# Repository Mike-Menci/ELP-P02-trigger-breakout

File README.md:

To trigger the camera as the nozzle passes over the vision area, your motion controller (e.g., Duet, Smoothieboard, or custom firmware) must:
Know the exact position of the nozzle.
Send a trigger pulse when the nozzle is centered over the camera FOV.
Optionally, queue the trigger slightly ahead to compensate for latency.
Example (pseudo-code):
if (motor->within_trigger_area()) {
    if (!trig_condition) {
        pull_camera_trig(); // Send 1.8V pulse
        trig_condition = true;
    }
}

This logic can be added to the stepper interrupt loop or motion planner in your firmware.

**** OpenPnP Software Integration
OpenPnP does not yet natively support on-the-fly vision, but you can prototype it with the following steps:
** Step-by-Step Integration Plan:
Disable Bottom Vision Settling
In OpenPnP, disable the default bottom vision settling behavior to allow motion to continue.
Use External Trigger Mode
Configure the camera to only capture when triggered (via hardware trigger), not on a free-running stream.
Capture Image Asynchronously
After triggering, store the image in a buffer (possibly on a companion MCU like ESP32 or Raspberry Pi) and notify OpenPnP when ready.
Process Image in Parallel
While the head moves to the placement location, process the image in a background thread to extract part offset and rotation.
Apply Correction at Placement
Use the vision result to adjust the final placement coordinates.
Note: OpenPnP currently processes vision synchronously, so you'll need to modify the pipeline or offload processing to avoid blocking motion

| Issue                   | Solution                                                                |
| ----------------------- | ----------------------------------------------------------------------- |
| **1.8V logic level**    | Use optocoupler or level shifter                                        |
| **USB bandwidth**       | Triggered mode reduces unnecessary frames                               |
| **Image buffer**        | Use a companion board (ESP32, RP2040, or RPi) to grab and hold images   |
| **OpenPnP integration** | Requires custom code or plugin to handle async vision                   |
| **Lighting**            | Use **external strobe LED** synced with trigger for consistent exposure |

Summary
To implement on-the-fly vision with ELP-USBGS1200P02 and OpenPnP:
Use P02 variant with 1.8V hardware trigger.
Modify motion controller firmware to send trigger at nozzle position.
Use external MCU to buffer images and notify OpenPnP.
Modify OpenPnP to process vision asynchronously and apply corrections at placement.
This is a complex but achievable upgrade..... The OpenPnP community is actively exploring this, especially with global shutter cameras like the ELP P02.
Sample circuit diagram for the trigger interface
Controller                         Camera
┌──────────┐                      ┌──────────┐
│  TRIG_IN │──R1──┐               │          │
│  3.3-5 V │      │  ┌------┐     │  1.8 V   │
└──────────┘      └──│+ LED │---- │  SYNC    │
                     │ PC817│     │  (TRIG)  │
GND ──────────────── │-     │     │          │
                     └------┘     └────┬─────┘
                          │           │
                          │ C1 100 nF │
                          │           │
                          └─[R2 1 kΩ]─┴──► to camera 1.8 V rail
                          │
                         GND (camera GND)
Parts list (0805 or through-hole)
OK = PC817 (or any 5 mA CTR ≥ 50 % opto)
R1 = 330 Ω (limits LED current @ 5 V to ≈ 10 mA)
R2 = 1 kΩ (pull-up to camera 1.8 V rail)
C1 = 100 nF (optional, debounce / 10 µs filter)
J1 = 2-pin header – controller side (“TRIG_IN”)
J2 = 2-pin header – camera side (SYNC & GND)

How it works
Idle: opto LED off → photo-transistor open → SYNC pulled to 1.8 V (camera idle).
Trigger pulse from controller (≥ 5 µs wide): LED turns on → transistor pulls SYNC to GND (active-low trigger).
Camera fires on falling edge of SYNC (1.8 V → 0 V).
Release controller pin → LED off → SYNC returns to 1.8 V → camera re-arms.

Board-level wiring for ELP-USBGS1200P02
The P02 variant brings the trigger out on a 5-pin JST-1.25 connector (bottom edge).
Pin-out (camera top-side silkscreen):
Table
Copy
Pin	Name	Wire colour (typ.)	Notes
1	GND	black	Common with USB shield
2	SYNC	white	Connect to “SYNC” node above
3	3.3 V	red	Ignore – this is an output from camera regulator
4	SDA	green	I²C for future use, leave open
5	SCL	yellow	I²C for future use, leave open
Only pins 1 & 2 are used for triggering.

******* Quick smoke test
Load v4l2-ctl --list-ctrls – confirm trigger_mode exists.
Set camera to external trigger:
v4l2-ctl -c trigger_mode=1
Toggle controller pin – you should see one frame appear in cheese / ffplay each time.

If you prefer a single-chip solution, replace the opto with a SN74LVC1T45 level-shifter powered from 1.8 V on the camera side; the wiring is identical, 
but the above schematic keeps you safe even if you accidentally short 24 V into the trigger line.

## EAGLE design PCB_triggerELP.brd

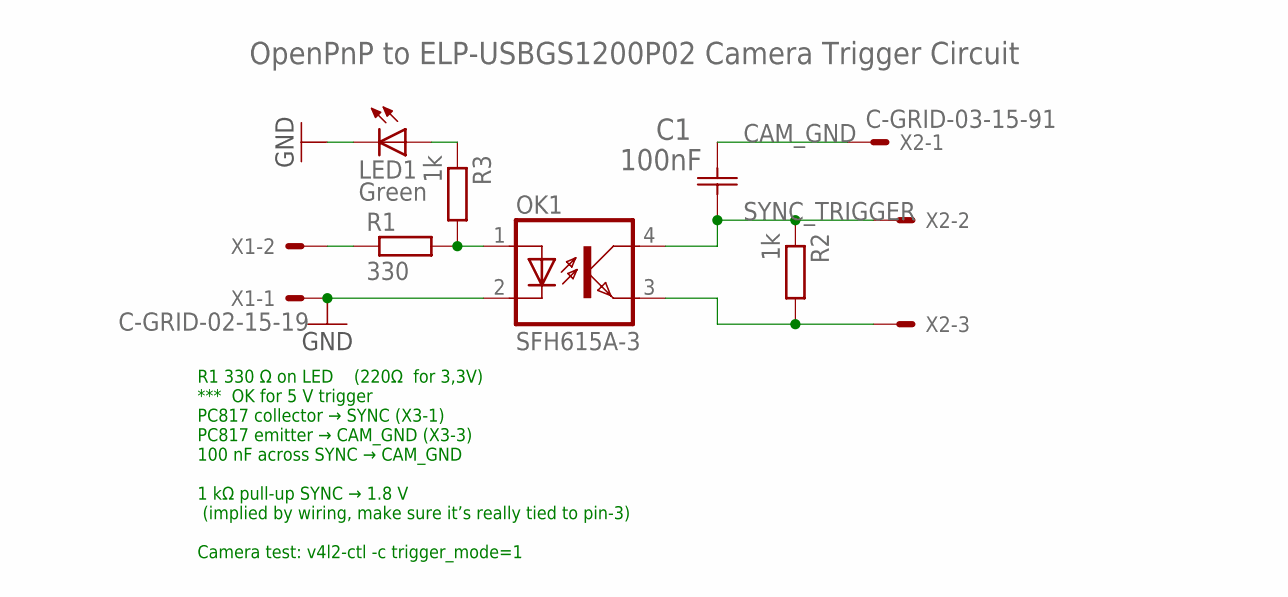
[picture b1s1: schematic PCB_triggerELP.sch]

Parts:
C1: 100nF; CAPC2012X140N
LED1: Green; CHIP-LED0603
OK1: SFH615A-3; SMD4-7
R1: 330; R0603
R2, R3: 1k; R0603
X1: C-GRID-02-15-19; 15-91-02
X2: C-GRID-03-15-91; 15-91-03

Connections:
CAM_GND: C1.2 (C2), X2.1
GND: LED1.C, OK1.2 (C), X1.1
unnamed: OK1.1 (A), R1.2, R3.2
unnamed: OK1.3 (EMIT), R2.2, X2.3
unnamed: LED1.A, R3.1
SYNC_TRIGGER: C1.1 (C1), OK1.4 (COL), R2.1, X2.2
TRIGGER_IN: R1.1, X1.2

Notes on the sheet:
R1 330 Ω on LED (220Ω for 3,3V) *** OK for 5 V trigger PC817 collector → SYNC (X3-1) PC817 emitter → CAM_GND (X3-3) 100 nF across SYNC → CAM_GND 1 kΩ pull-up SYNC → 1.8 V (implied by wiring, make sure it’s really tied to pin-3) Camera test: v4l2-ctl -c trigger_mode=1
OpenPnP to ELP‑USBGS1200P02 Camera Trigger Circuit

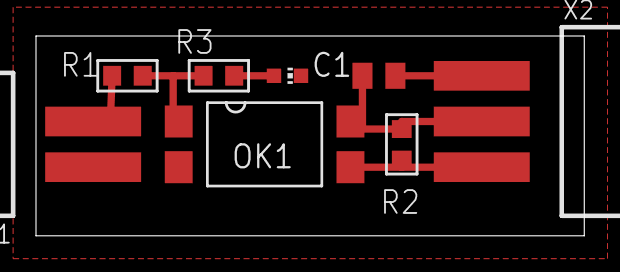
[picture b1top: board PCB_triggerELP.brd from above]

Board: 2 copper layers, 30.5 x 11.1 mm, 8 parts (0 on the bottom side), 7 nets.

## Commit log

2025-09-13 Add files via upload
    Documents
2025-09-13 ELP-P02 README.md
    description:
